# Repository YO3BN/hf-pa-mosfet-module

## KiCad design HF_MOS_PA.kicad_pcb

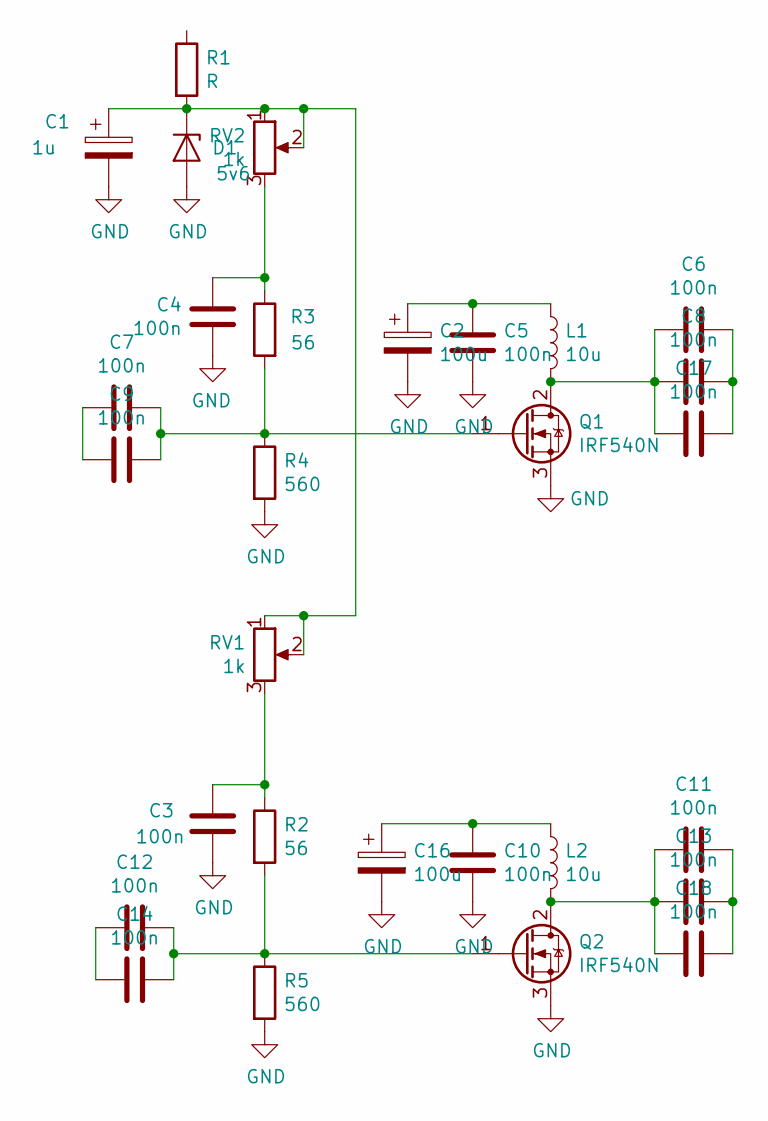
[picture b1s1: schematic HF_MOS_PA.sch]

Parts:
C1: 1u; CP_Elec_4x5.3
C2, C16: 100u; CP_Elec_8x10
C3, C4, C5, C6, C7, C8, C9, C10, C11, C12, C13, C14, C17, C18: 100n; C_1206_3216Metric_Pad1.42x1.75mm_HandSolder
D1: 5v6; D_1206_3216Metric_Pad1.42x1.75mm_HandSolder
L1, L2: 10u; L_Bourns-SRR1005
Q1, Q2: IRF540N; TO-220-3_Vertical
R1: R; R_1206_3216Metric_Pad1.42x1.75mm_HandSolder
R2, R3: 56; R_1206_3216Metric_Pad1.42x1.75mm_HandSolder
R4, R5: 560; R_1206_3216Metric_Pad1.42x1.75mm_HandSolder
RV1, RV2: 1k; Potentiometer_Bourns_3314R-GM5_Vertical

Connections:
GND: C1.2, C2.2, C3.2, C4.2, C5.2, C10.2, C16.2, D1.2 (A), Q1.3 (S), Q2.3 (S), R4.2, R5.2; also elsewhere on the board
unnamed: C1.1, D1.1 (K), R1.2, RV1.1, RV1.2, RV2.1, RV2.2
unnamed: C2.1, C5.1, L1.1
unnamed: C3.1, R2.1, RV1.3
unnamed: C4.1, R3.1, RV2.3
unnamed: C7.1, C9.1
unnamed: C7.2, C9.2, Q1.1 (G), R3.2, R4.1
unnamed: C10.1, C16.1, L2.1
unnamed: C11.1, C13.1, C18.2, L2.2, Q2.2 (D)
unnamed: C11.2, C13.2, C18.1
unnamed: C12.1, C14.1
unnamed: C12.2, C14.2, Q2.1 (G), R2.2, R5.1
unnamed: C6.2, C8.2, C17.1
unnamed: C6.1, C8.1, C17.2, L1.2, Q1.2 (D)

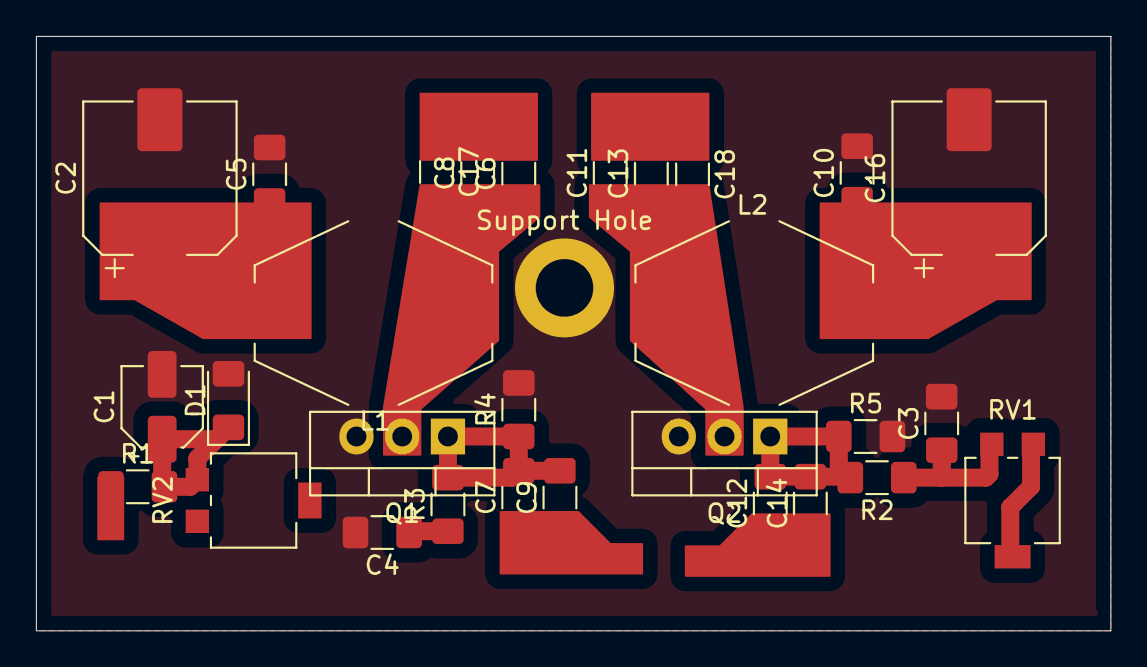
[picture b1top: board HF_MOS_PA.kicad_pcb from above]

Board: 2 copper layers, 59.7 x 33.0 mm, 30 parts (0 on the bottom side), 14 nets.

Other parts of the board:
Support Hole: MountingHole_3.2mm_M3_ISO14580_Pad

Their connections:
GND: Support Hole.1; also elsewhere on the board

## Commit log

2022-10-12 First commit.
